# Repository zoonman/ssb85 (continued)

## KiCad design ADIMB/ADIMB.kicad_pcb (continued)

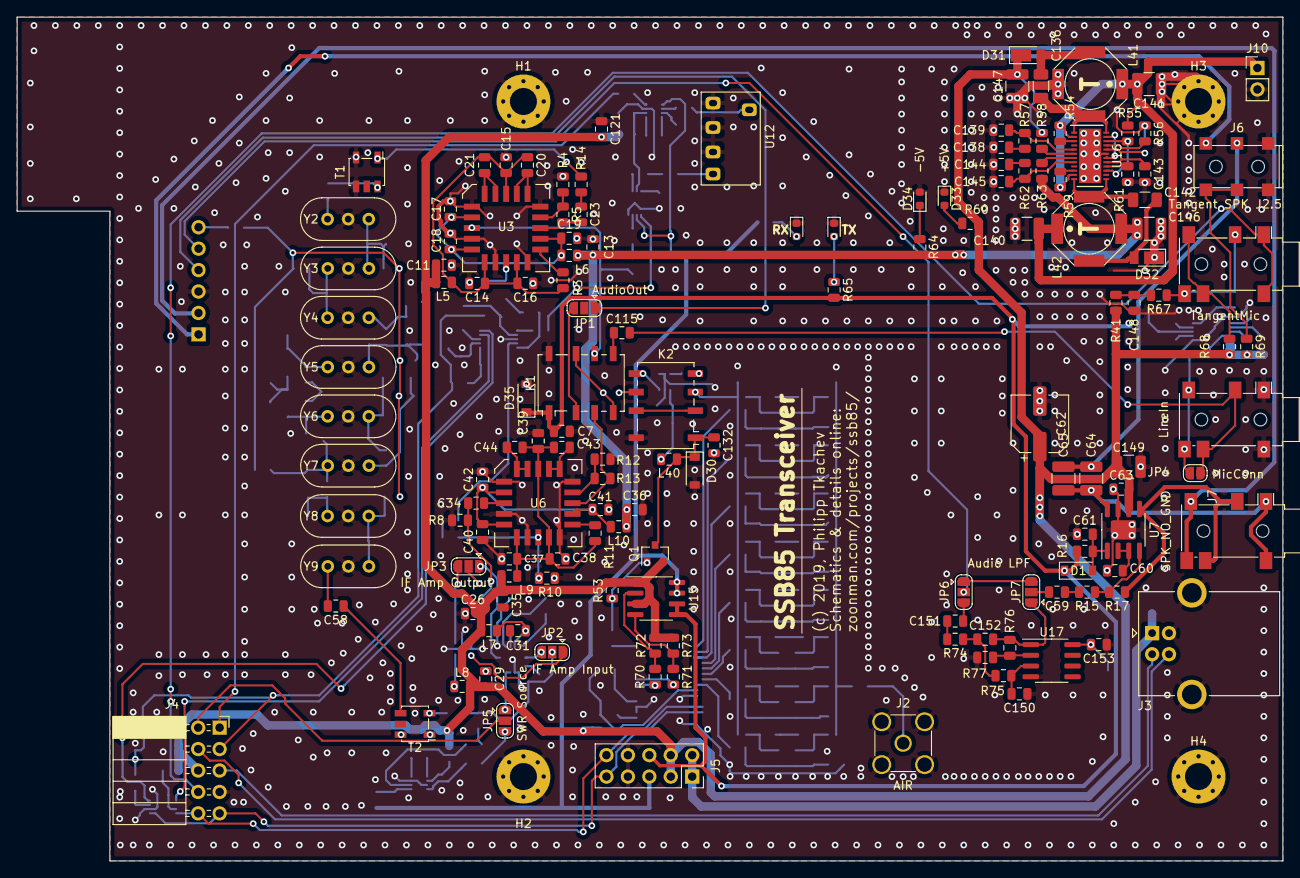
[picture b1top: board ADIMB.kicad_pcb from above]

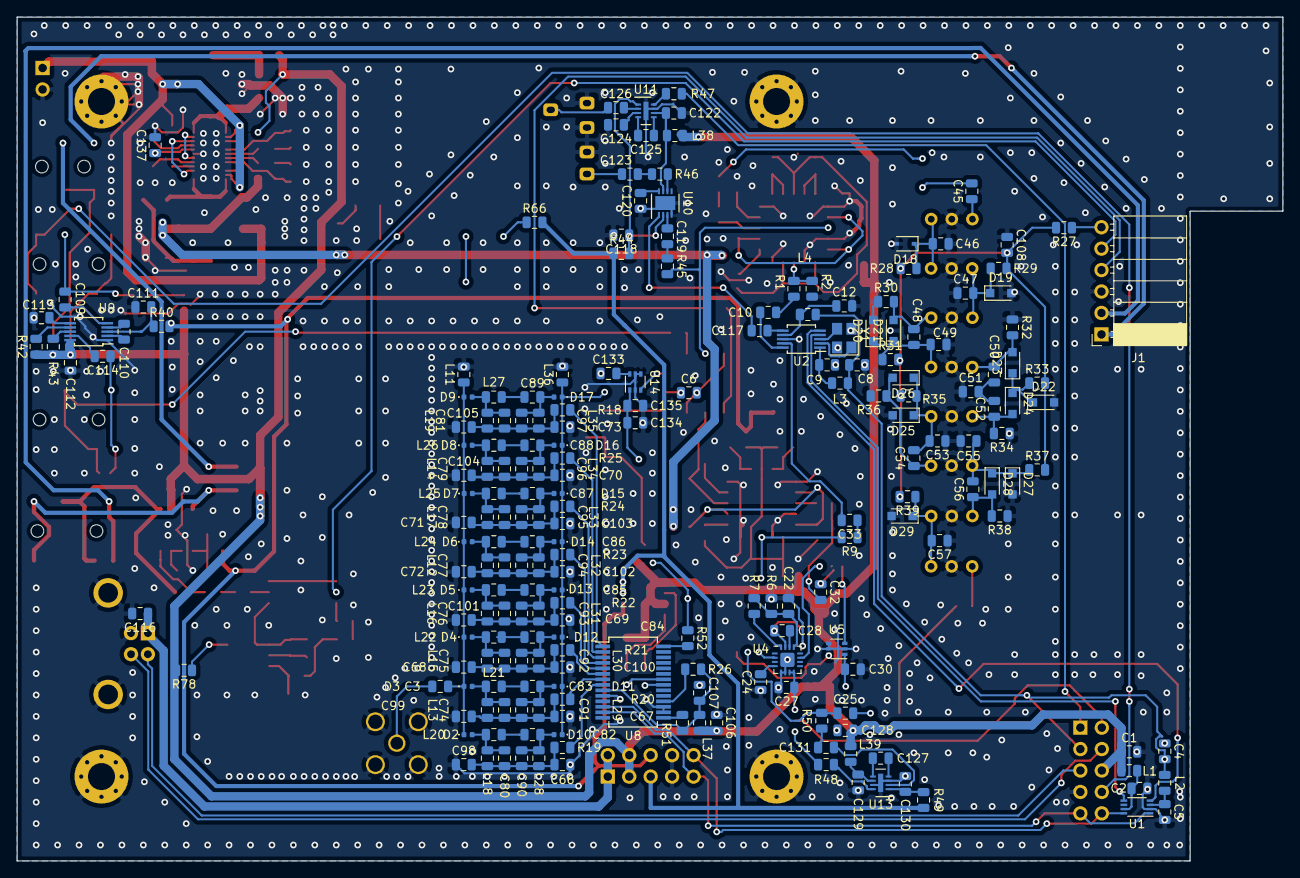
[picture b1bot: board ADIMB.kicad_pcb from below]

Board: 2 copper layers, 150.0 x 100.0 mm, 362 parts (213 on the bottom side), 223 nets.
